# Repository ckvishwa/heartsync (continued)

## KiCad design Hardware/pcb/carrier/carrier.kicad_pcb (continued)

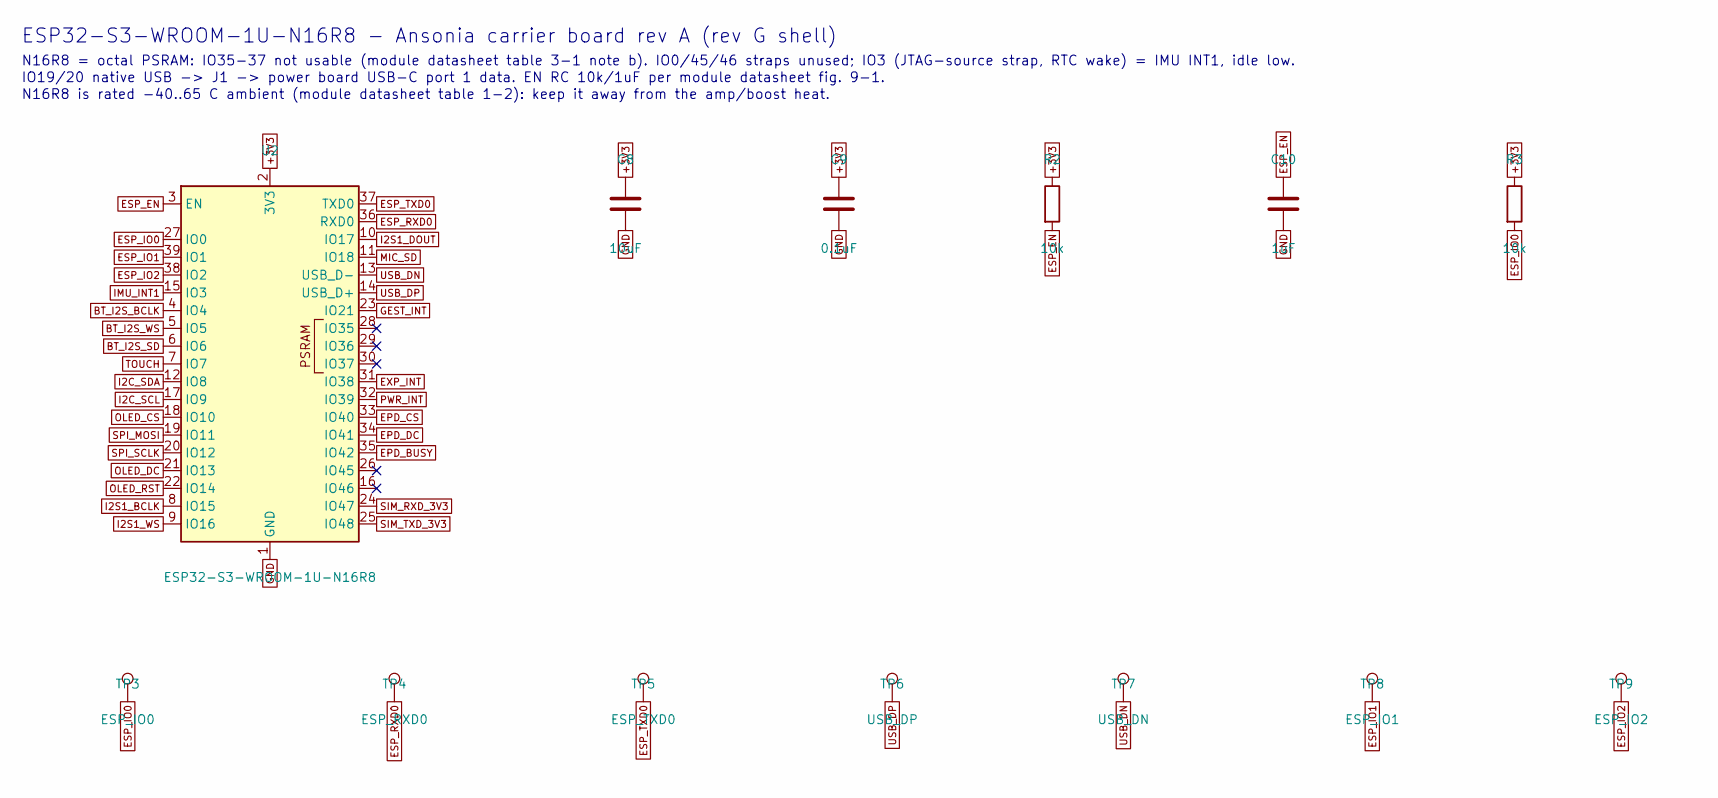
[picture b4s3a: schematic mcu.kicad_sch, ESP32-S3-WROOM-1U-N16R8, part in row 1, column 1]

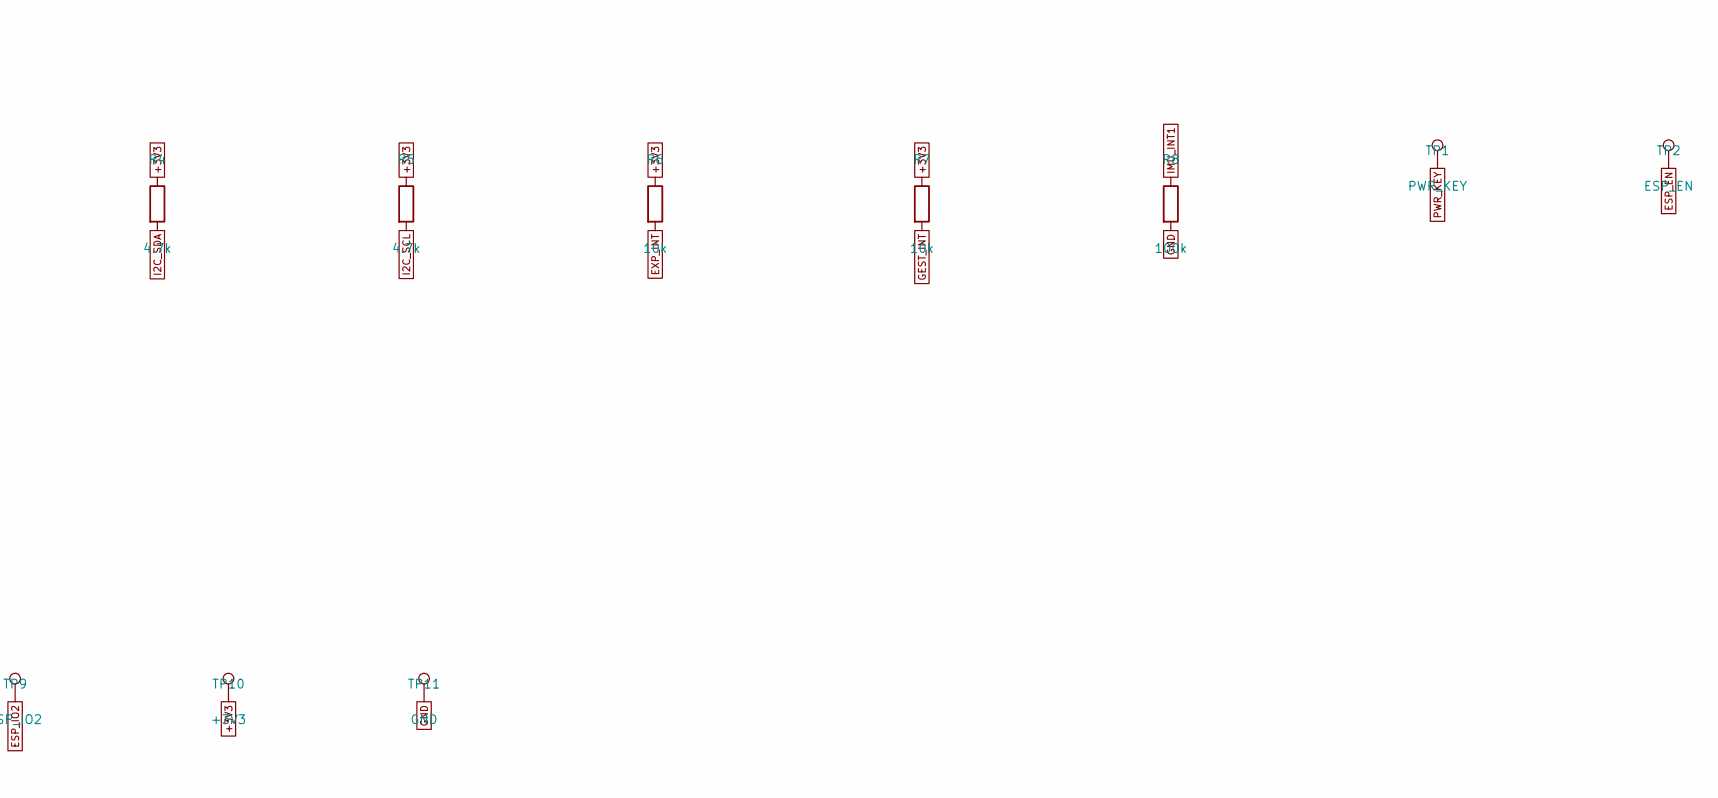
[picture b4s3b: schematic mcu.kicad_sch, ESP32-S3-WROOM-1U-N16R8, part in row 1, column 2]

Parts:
C8: 10uF; C_0603_1608Metric
C9: 0.1uF; C_0402_1005Metric
C10: 1uF; C_0402_1005Metric
R2, R3, R6, R7: 10k; R_0402_1005Metric
R4, R5: 4.7k; R_0402_1005Metric
R8: 100k; R_0402_1005Metric
TP1: PWR_KEY; TestPoint_Pad_D1.0mm
TP2: ESP_EN; TestPoint_Pad_D1.0mm
TP3: ESP_IO0; TestPoint_Pad_D1.0mm
TP4: ESP_RXD0; TestPoint_Pad_D1.0mm
TP5: ESP_TXD0; TestPoint_Pad_D1.0mm
TP6: USB_DP; TestPoint_Pad_D1.0mm
TP7: USB_DN; TestPoint_Pad_D1.0mm
TP8: ESP_IO1; TestPoint_Pad_D1.0mm
TP9: ESP_IO2; TestPoint_Pad_D1.0mm
TP10: +3V3; TestPoint_Pad_D1.0mm
TP11: GND; TestPoint_Pad_D1.0mm
U2: ESP32-S3-WROOM-1U-N16R8; ESP32-S3-WROOM-1U_NoVias; MPN ESP32-S3-WROOM-1U-N16R8; LCSC C3013946

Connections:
+3V3: C8.1, C9.1, R2.1, R3.1, R4.1, R5.1, R6.1, R7.1, TP10.1, U2.2 (3V3); also elsewhere on the board
BT_I2S_BCLK: U2.4 (IO4); also elsewhere on the board
BT_I2S_SD: U2.6 (IO6); also elsewhere on the board
BT_I2S_WS: U2.5 (IO5); also elsewhere on the board
EPD_BUSY: U2.35 (IO42); also elsewhere on the board
EPD_CS: U2.33 (IO40); also elsewhere on the board
EPD_DC: U2.34 (IO41); also elsewhere on the board
ESP_EN: C10.1, R2.2, TP2.1, U2.3 (EN)
ESP_IO0: R3.2, TP3.1, U2.27 (IO0)
ESP_IO1: TP8.1, U2.39 (IO1)
ESP_IO2: TP9.1, U2.38 (IO2)
ESP_RXD0: TP4.1, U2.36 (RXD0)
ESP_TXD0: TP5.1, U2.37 (TXD0)
EXP_INT: R6.2, U2.31 (IO38); also elsewhere on the board
GEST_INT: R7.2, U2.23 (IO21); also elsewhere on the board
GND: C8.2, C9.2, C10.2, R8.2, TP11.1, U2.1 (GND), U2.40 (GND), U2.41 (GND); also elsewhere on the board
I2C_SCL: R5.2, U2.17 (IO9); also elsewhere on the board
I2C_SDA: R4.2, U2.12 (IO8); also elsewhere on the board
I2S1_BCLK: U2.8 (IO15); also elsewhere on the board
I2S1_DOUT: U2.10 (IO17); also elsewhere on the board
I2S1_WS: U2.9 (IO16); also elsewhere on the board
IMU_INT1: R8.1, U2.15 (IO3); also elsewhere on the board
MIC_SD: U2.11 (IO18); also elsewhere on the board
OLED_CS: U2.18 (IO10); also elsewhere on the board
OLED_DC: U2.21 (IO13); also elsewhere on the board
OLED_RST: U2.22 (IO14); also elsewhere on the board
PWR_INT: U2.32 (IO39); also elsewhere on the board
PWR_KEY: TP1.1; also elsewhere on the board
SIM_RXD_3V3: U2.24 (IO47); also elsewhere on the board
SIM_TXD_3V3: U2.25 (IO48); also elsewhere on the board
SPI_MOSI: U2.19 (IO11); also elsewhere on the board
SPI_SCLK: U2.20 (IO12); also elsewhere on the board
TOUCH: U2.7 (IO7); also elsewhere on the board
USB_DN: TP7.1, U2.13 (USB_D-); also elsewhere on the board
USB_DP: TP6.1, U2.14 (USB_D+); also elsewhere on the board

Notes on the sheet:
ESP32-S3-WROOM-1U-N16R8 - Ansonia carrier board rev A (rev G shell)
N16R8 = octal PSRAM: IO35-37 not usable (module datasheet table 3-1 note b). IO0/45/46 straps unused; IO3 (JTAG-source strap, RTC wake) = IMU INT1, idle low.
IO19/20 native USB -> J1 -> power board USB-C port 1 data. EN RC 10k/1uF per module datasheet fig. 9-1.
N16R8 is rated -40..65 C ambient (module datasheet table 1-2): keep it away from the amp/boost heat.

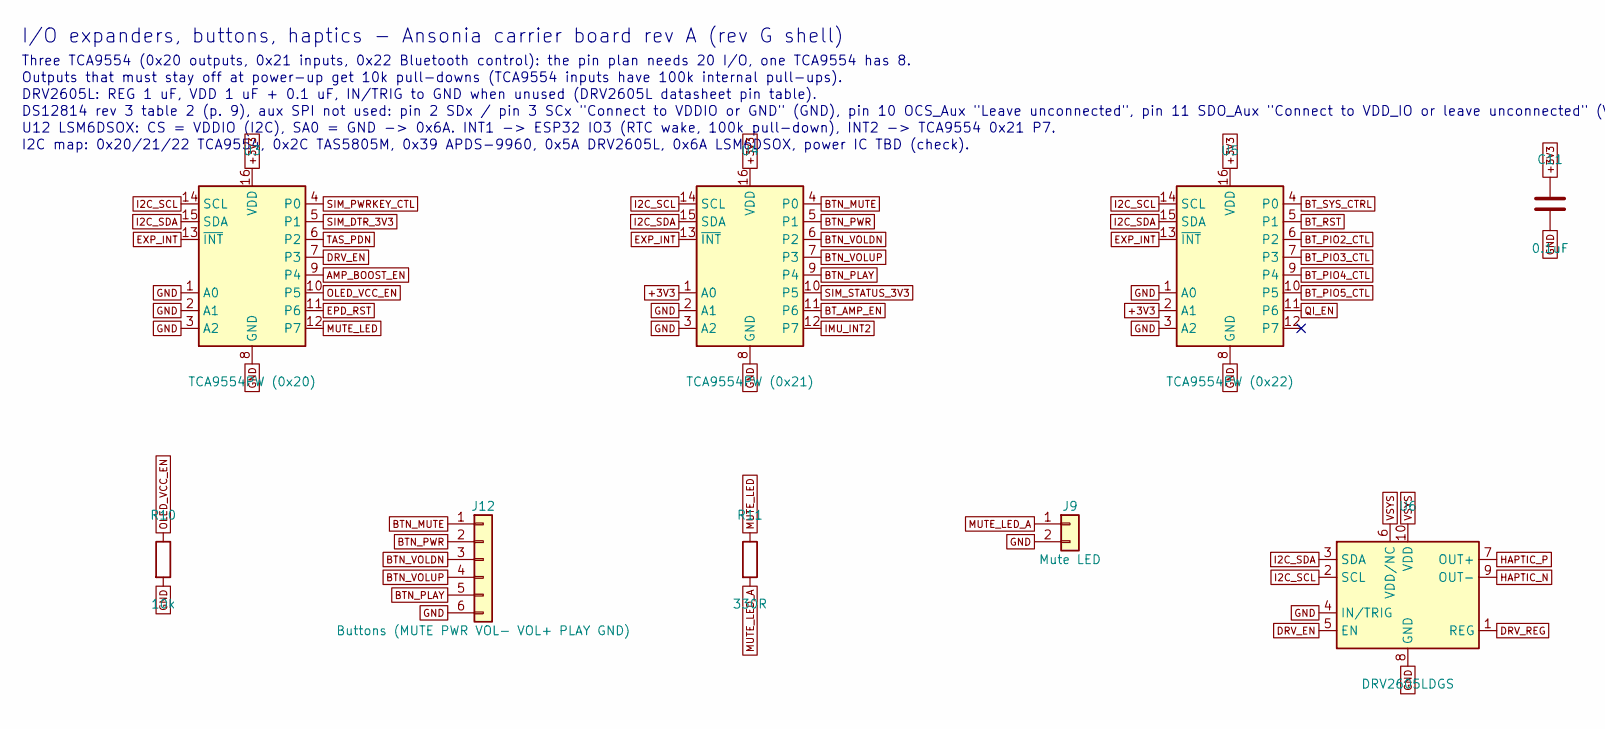
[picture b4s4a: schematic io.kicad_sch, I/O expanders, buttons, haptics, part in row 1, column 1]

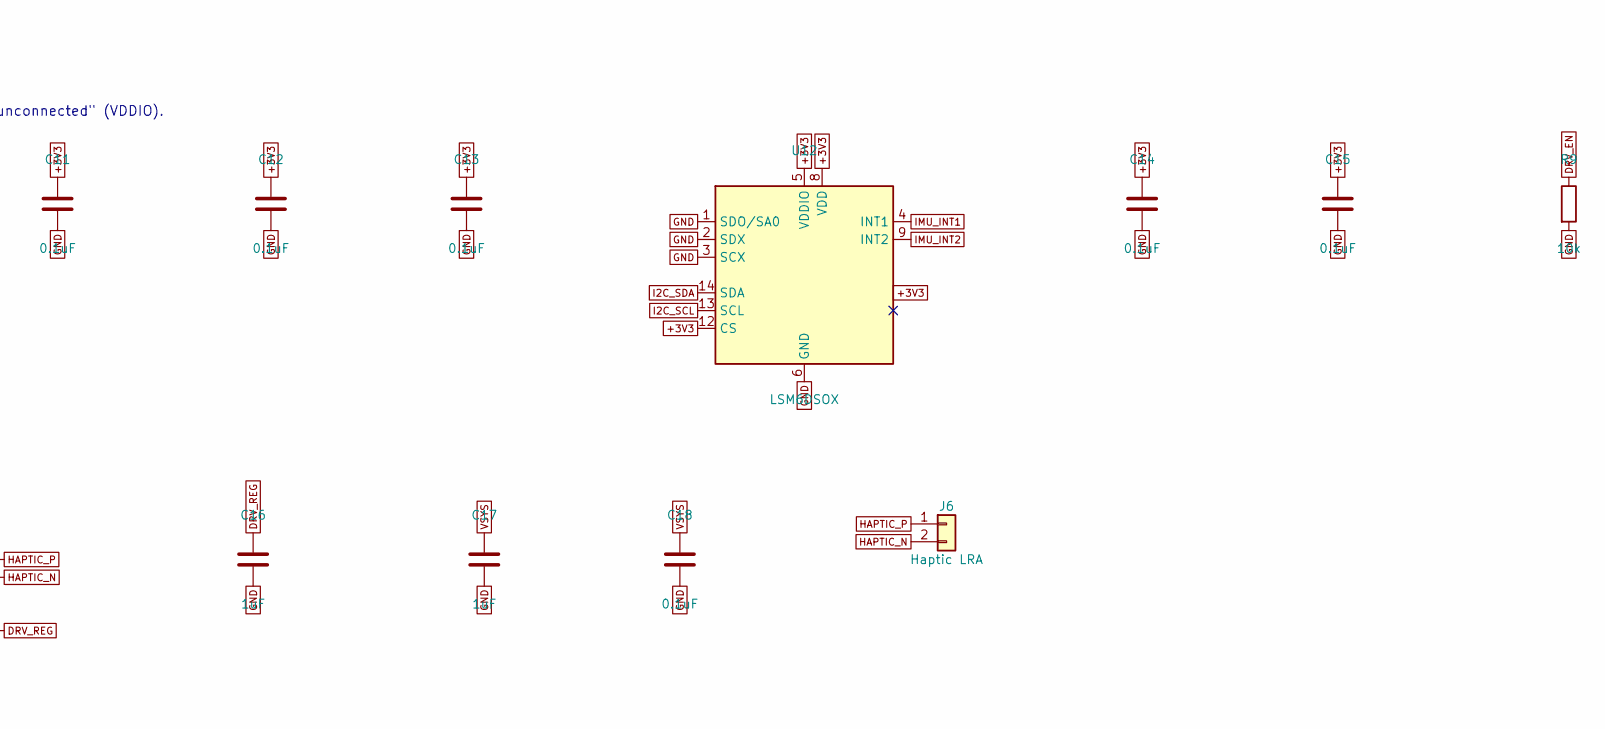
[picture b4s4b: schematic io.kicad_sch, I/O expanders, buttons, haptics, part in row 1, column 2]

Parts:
C11, C12, C13, C14, C15, C18: 0.1uF; C_0402_1005Metric
C16, C17: 1uF; C_0402_1005Metric
J6: Haptic LRA; JST_SH_SM02B-SRSS-TB_1x02-1MP_P1.00mm_Horizontal
J9: Mute LED; JST_SH_SM02B-SRSS-TB_1x02-1MP_P1.00mm_Horizontal
J12: Buttons (MUTE PWR VOL- VOL+ PLAY GND); JST_SH_SM06B-SRSS-TB_1x06-1MP_P1.00mm_Horizontal
R9, R10: 10k; R_0402_1005Metric
R11: 330R; R_0402_1005Metric
U3: TCA9554PW (0x20); TSSOP-16_4.4x5mm_P0.65mm; MPN TCA9554PWR; LCSC C86803
U4: TCA9554PW (0x21); TSSOP-16_4.4x5mm_P0.65mm; MPN TCA9554PWR; LCSC C86803
U5: TCA9554PW (0x22); TSSOP-16_4.4x5mm_P0.65mm; MPN TCA9554PWR; LCSC C86803
U6: DRV2605LDGS; TSSOP-10_3x3mm_P0.5mm; MPN DRV2605LDGSR; LCSC C527464
U12: LSM6DSOX; LGA-14_3x2.5mm_P0.5mm_LayoutBorder3x4y; MPN LSM6DSOXTR

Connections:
+3V3: C11.1, C12.1, C13.1, C14.1, C15.1, U3.16 (VDD), U4.1 (A0), U4.16 (VDD), U5.2 (A1), U5.16 (VDD), U12.5 (VDDIO), U12.8 (VDD), U12.11 (SDO_Aux), U12.12 (CS); also elsewhere on the board
AMP_BOOST_EN: U3.9 (P4); also elsewhere on the board
BTN_MUTE: J12.1, U4.4 (P0)
BTN_PLAY: J12.5, U4.9 (P4)
BTN_PWR: J12.2, U4.5 (P1)
BTN_VOLDN: J12.3, U4.6 (P2)
BTN_VOLUP: J12.4, U4.7 (P3)
BT_AMP_EN: U4.11 (P6); also elsewhere on the board
BT_PIO2_CTL: U5.6 (P2); also elsewhere on the board
BT_PIO3_CTL: U5.7 (P3); also elsewhere on the board
BT_PIO4_CTL: U5.9 (P4); also elsewhere on the board
BT_PIO5_CTL: U5.10 (P5); also elsewhere on the board
BT_RST: U5.5 (P1); also elsewhere on the board
BT_SYS_CTRL: U5.4 (P0); also elsewhere on the board
DRV_EN: R9.1, U3.7 (P3), U6.5 (EN)
DRV_REG: C16.1, U6.1 (REG)
EPD_RST: U3.11 (P6); also elsewhere on the board
EXP_INT: U3.13 (~INT), U4.13 (~INT), U5.13 (~INT); also elsewhere on the board
GND: C11.2, C12.2, C13.2, C14.2, C15.2, C16.2, C17.2, C18.2, J9.2, J12.6, R9.2, R10.2, U3.1 (A0), U3.2 (A1), U3.3 (A2), U3.8 (GND), U4.2 (A1), U4.3 (A2), U4.8 (GND), U5.1 (A0), U5.3 (A2), U5.8 (GND), U6.4 (IN/TRIG), U6.8 (GND), U12.1 (SDO/SA0), U12.2 (SDX), U12.3 (SCX), U12.6 (GND), U12.7 (GND); also elsewhere on the board
HAPTIC_N: J6.2, U6.9 (OUT-)
HAPTIC_P: J6.1, U6.7 (OUT+)
I2C_SCL: U3.14 (SCL), U4.14 (SCL), U5.14 (SCL), U6.2 (SCL), U12.13 (SCL); also elsewhere on the board
I2C_SDA: U3.15 (SDA), U4.15 (SDA), U5.15 (SDA), U6.3 (SDA), U12.14 (SDA); also elsewhere on the board
IMU_INT1: U12.4 (INT1); also elsewhere on the board
IMU_INT2: U4.12 (P7), U12.9 (INT2)
MUTE_LED: R11.1, U3.12 (P7)
MUTE_LED_A: J9.1, R11.2
OLED_VCC_EN: R10.1, U3.10 (P5); also elsewhere on the board
QI_EN: U5.11 (P6); also elsewhere on the board
SIM_DTR_3V3: U3.5 (P1); also elsewhere on the board
SIM_PWRKEY_CTL: U3.4 (P0); also elsewhere on the board
SIM_STATUS_3V3: U4.10 (P5); also elsewhere on the board
TAS_PDN: U3.6 (P2); also elsewhere on the board
VSYS: C17.1, C18.1, U6.6 (VDD/NC), U6.10 (VDD); also elsewhere on the board

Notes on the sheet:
I/O expanders, buttons, haptics - Ansonia carrier board rev A (rev G shell)
Three TCA9554 (0x20 outputs, 0x21 inputs, 0x22 Bluetooth control): the pin plan needs 20 I/O, one TCA9554 has 8.
Outputs that must stay off at power-up get 10k pull-downs (TCA9554 inputs have 100k internal pull-ups).
DRV2605L: REG 1 uF, VDD 1 uF + 0.1 uF, IN/TRIG to GND when unused (DRV2605L datasheet pin table).
DS12814 rev 3 table 2 (p. 9), aux SPI not used: pin 2 SDx / pin 3 SCx "Connect to VDDIO or GND" (GND), pin 10 OCS_Aux "Leave unconnected", pin 11 SDO_Aux "Connect to VDD_IO or leave unconnected" (VDDIO).
U12 LSM6DSOX: CS = VDDIO (I2C), SA0 = GND -> 0x6A. INT1 -> ESP32 IO3 (RTC wake, 100k pull-down), INT2 -> TCA9554 0x21 P7.
I2C map: 0x20/21/22 TCA9554, 0x2C TAS5805M, 0x39 APDS-9960, 0x5A DRV2605L, 0x6A LSM6DSOX, power IC TBD (check).

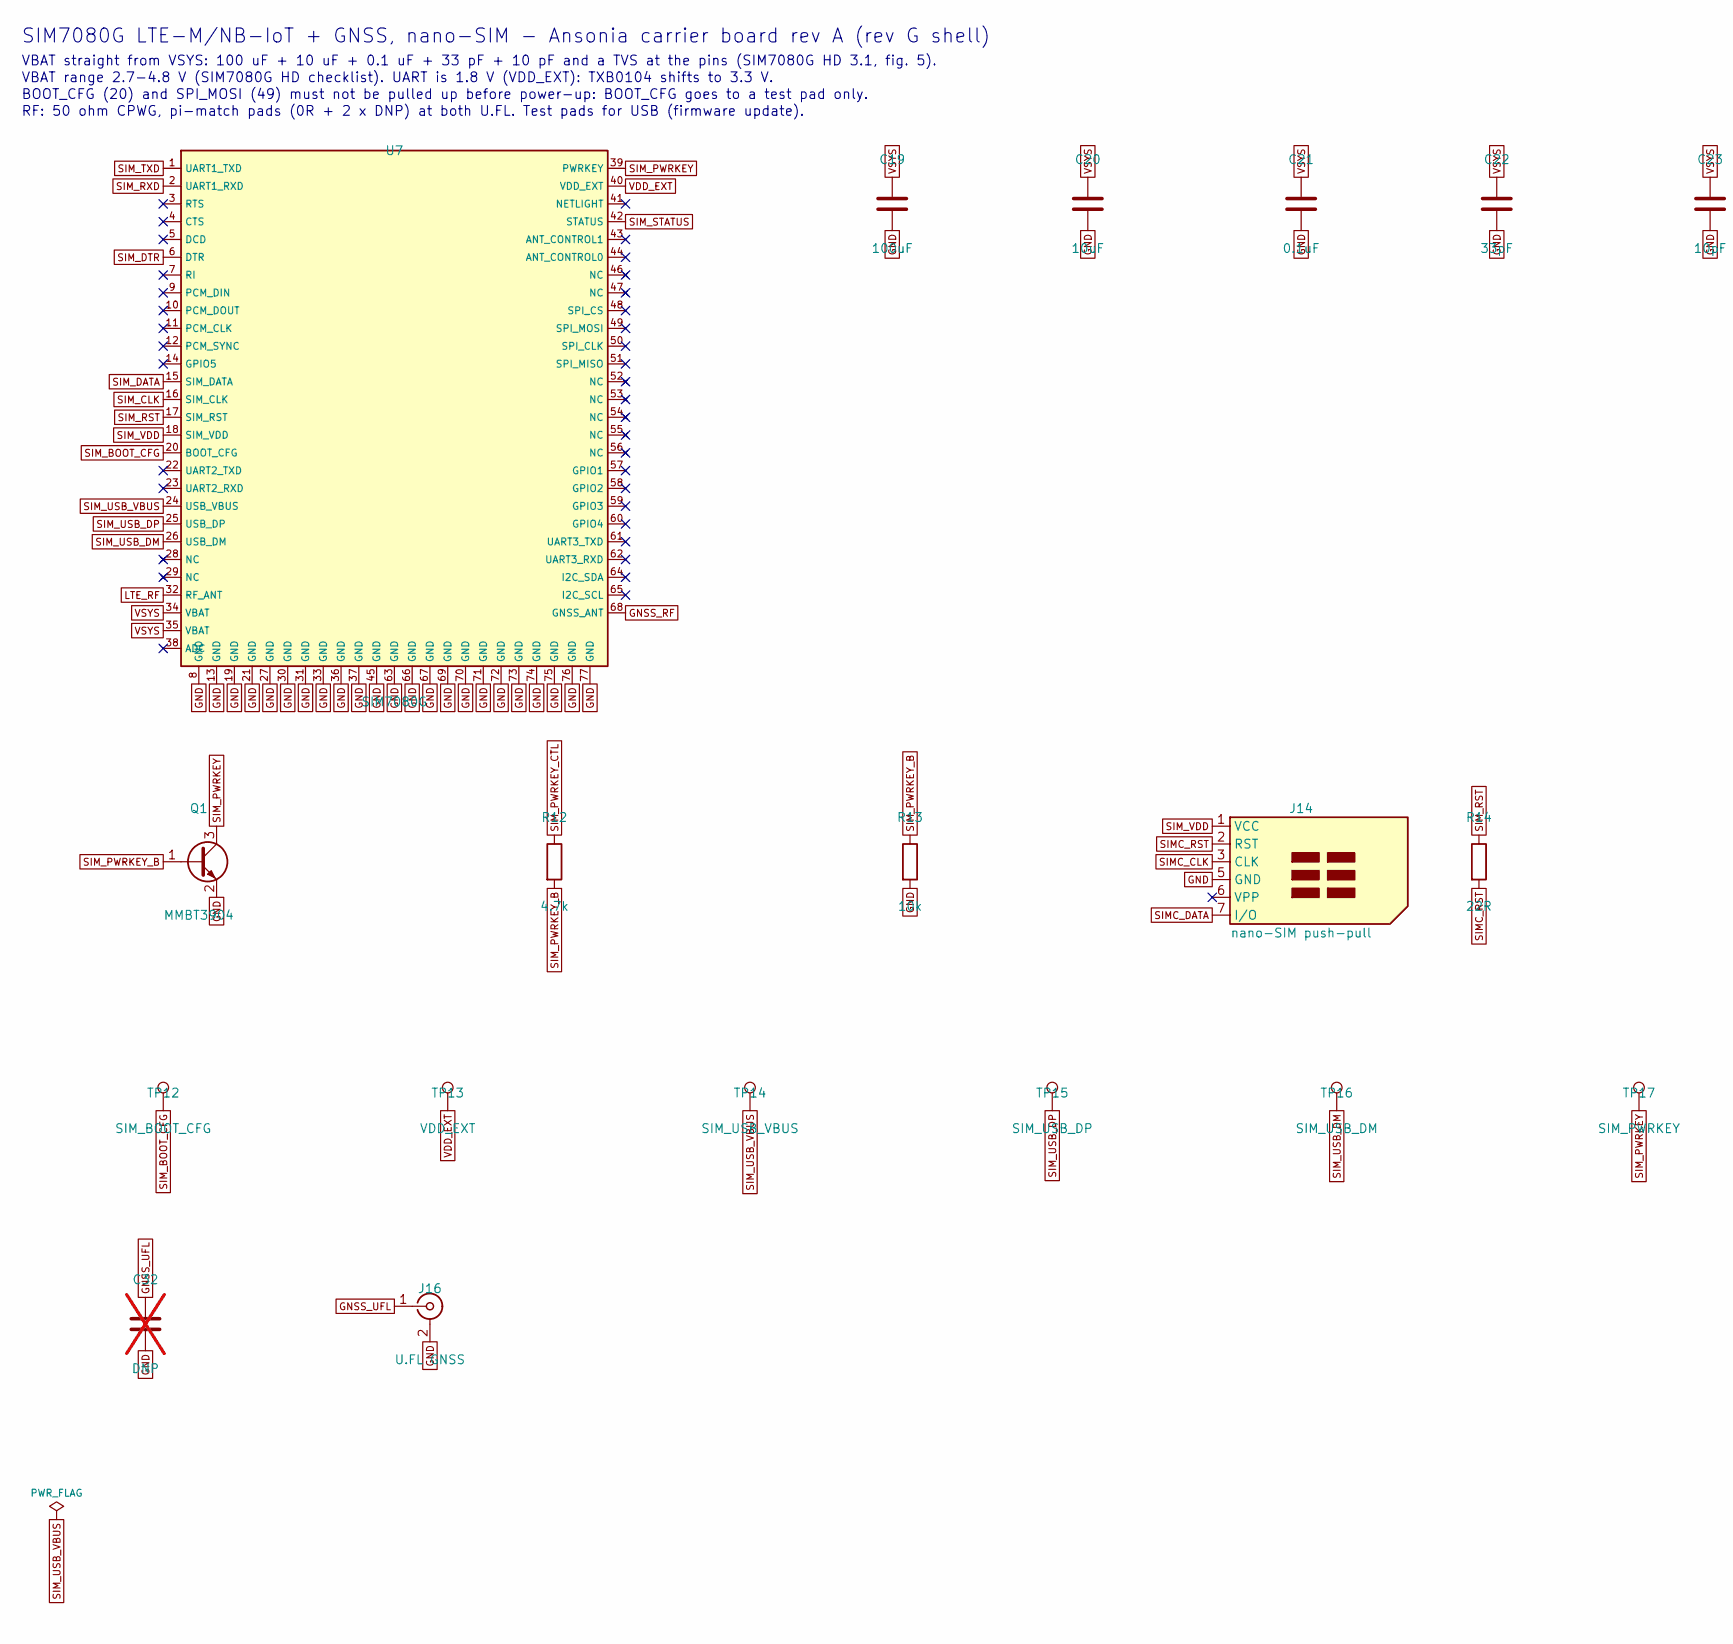
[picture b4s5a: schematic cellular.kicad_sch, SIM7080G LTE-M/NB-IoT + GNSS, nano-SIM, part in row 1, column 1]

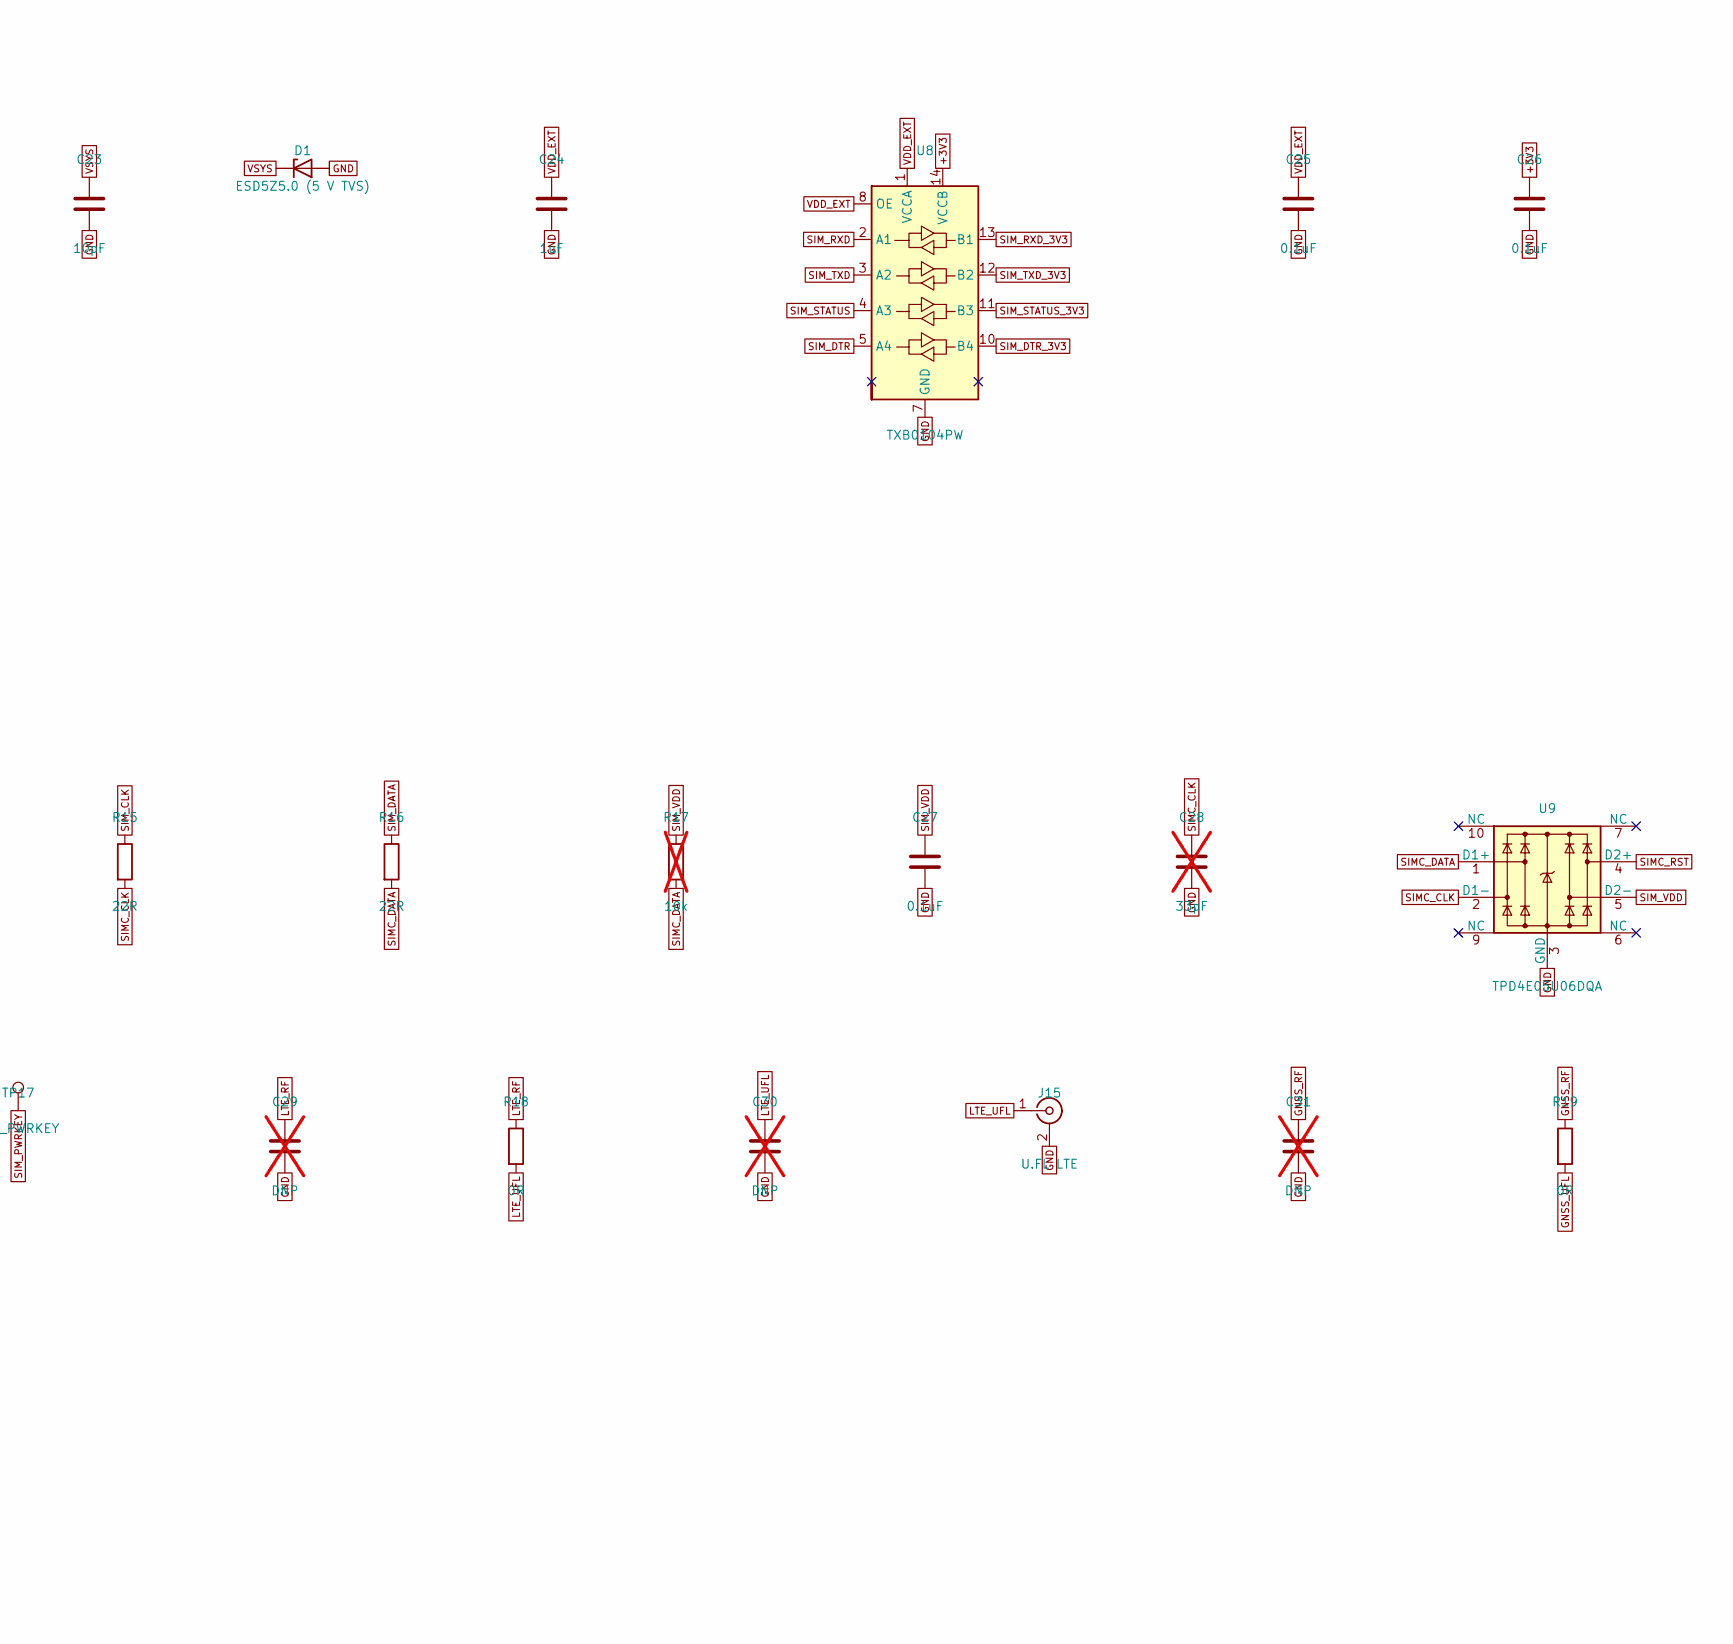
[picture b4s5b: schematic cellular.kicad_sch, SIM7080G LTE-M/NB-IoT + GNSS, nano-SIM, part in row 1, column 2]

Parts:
C19: 100uF; C_1210_3225Metric
C20: 10uF; C_0603_1608Metric
C21, C25, C26, C27: 0.1uF; C_0402_1005Metric
C22: 33pF; C_0402_1005Metric
C23: 10pF; C_0402_1005Metric
C24: 1uF; C_0402_1005Metric
C28: 33pF; C_0402_1005Metric; not fitted
C29, C30, C31, C32: DNP; C_0402_1005Metric; not fitted
D1: ESD5Z5.0 (5 V TVS); D_SOD-523
J14: nano-SIM push-pull; nanoSIM_GCT_SIM8060-6-0-14-00; MPN SIM8060-6-0-14-00-A
J15: U.FL LTE; U.FL_Hirose_U.FL-R-SMT-1_Vertical; MPN U.FL-R-SMT-1(10)
J16: U.FL GNSS; U.FL_Hirose_U.FL-R-SMT-1_Vertical; MPN U.FL-R-SMT-1(10)
Q1: MMBT3904; SOT-23
R12: 4.7k; R_0402_1005Metric
R13: 10k; R_0402_1005Metric
R14, R15, R16: 22R; R_0402_1005Metric
R17: 10k; R_0402_1005Metric; not fitted
R18, R19: 0R; R_0402_1005Metric
TP12: SIM_BOOT_CFG; TestPoint_Pad_D1.0mm
TP13: VDD_EXT; TestPoint_Pad_D1.0mm
TP14: SIM_USB_VBUS; TestPoint_Pad_D1.0mm
TP15: SIM_USB_DP; TestPoint_Pad_D1.0mm
TP16: SIM_USB_DM; TestPoint_Pad_D1.0mm
TP17: SIM_PWRKEY; TestPoint_Pad_D1.0mm
U7: SIM7080G; MPN SIM7080G; LCSC C2687012
U8: TXB0104PW; TSSOP-14_4.4x5mm_P0.65mm; MPN TXB0104PWR; LCSC C53406
U9: TPD4E05U06DQA; USON-10_2.5x1.0mm_P0.5mm; MPN TPD4E05U06DQAR

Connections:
+3V3: C26.1, U8.14 (VCCB); also elsewhere on the board
GND: C19.2, C20.2, C21.2, C22.2, C23.2, C24.2, C25.2, C26.2, C27.2, C28.2, C29.2, C30.2, C31.2, C32.2, D1.2 (A), J14.5 (GND), J15.2 (Ext), J16.2 (Ext), Q1.2 (E), R13.2, U7.8 (GND), U7.13 (GND), U7.19 (GND), U7.21 (GND), U7.27 (GND), U7.30 (GND), U7.31 (GND), U7.33 (GND), U7.36 (GND), U7.37 (GND), U7.45 (GND), U7.63 (GND), U7.66 (GND), U7.67 (GND), U7.69 (GND), U7.70 (GND), U7.71 (GND), U7.72 (GND), U7.73 (GND), U7.74 (GND), U7.75 (GND), U7.76 (GND), U7.77 (GND), U8.7 (GND), U9.3 (GND), U9.8 (GND); also elsewhere on the board
GNSS_RF: C31.1, R19.1, U7.68 (GNSS_ANT)
GNSS_UFL: C32.1, J16.1 (In), R19.2
LTE_RF: C29.1, R18.1, U7.32 (RF_ANT)
LTE_UFL: C30.1, J15.1 (In), R18.2
SIMC_CLK: C28.1, J14.3 (CLK), R15.2, U9.2 (D1-)
SIMC_DATA: J14.7 (I/O), R16.2, R17.2, U9.1 (D1+)
SIMC_RST: J14.2 (RST), R14.2, U9.4 (D2+)
SIM_BOOT_CFG: TP12.1, U7.20 (BOOT_CFG)
SIM_CLK: R15.1, U7.16 (SIM_CLK)
SIM_DATA: R16.1, U7.15 (SIM_DATA)
SIM_DTR: U7.6 (DTR), U8.5 (A4)
SIM_DTR_3V3: U8.10 (B4); also elsewhere on the board
SIM_PWRKEY: Q1.3 (C), TP17.1, U7.39 (PWRKEY)
SIM_PWRKEY_B: Q1.1 (B), R12.2, R13.1
SIM_PWRKEY_CTL: R12.1; also elsewhere on the board
SIM_RST: R14.1, U7.17 (SIM_RST)
SIM_RXD: U7.2 (UART1_RXD), U8.2 (A1)
SIM_RXD_3V3: U8.13 (B1); also elsewhere on the board
SIM_STATUS: U7.42 (STATUS), U8.4 (A3)
SIM_STATUS_3V3: U8.11 (B3); also elsewhere on the board
SIM_TXD: U7.1 (UART1_TXD), U8.3 (A2)
SIM_TXD_3V3: U8.12 (B2); also elsewhere on the board
SIM_USB_DM: TP16.1, U7.26 (USB_DM)
SIM_USB_DP: TP15.1, U7.25 (USB_DP)
SIM_USB_VBUS: TP14.1, U7.24 (USB_VBUS)
SIM_VDD: C27.1, J14.1 (VCC), R17.1, U7.18 (SIM_VDD), U9.5 (D2-)
VDD_EXT: C24.1, C25.1, TP13.1, U7.40 (VDD_EXT), U8.1 (VCCA), U8.8 (OE)
VSYS: C19.1, C20.1, C21.1, C22.1, C23.1, D1.1 (K), U7.34 (VBAT), U7.35 (VBAT); also elsewhere on the board

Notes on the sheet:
SIM7080G LTE-M/NB-IoT + GNSS, nano-SIM - Ansonia carrier board rev A (rev G shell)
VBAT straight from VSYS: 100 uF + 10 uF + 0.1 uF + 33 pF + 10 pF and a TVS at the pins (SIM7080G HD 3.1, fig. 5).
VBAT range 2.7-4.8 V (SIM7080G HD checklist). UART is 1.8 V (VDD_EXT): TXB0104 shifts to 3.3 V.
BOOT_CFG (20) and SPI_MOSI (49) must not be pulled up before power-up: BOOT_CFG goes to a test pad only.
RF: 50 ohm CPWG, pi-match pads (0R + 2 x DNP) at both U.FL. Test pads for USB (firmware update).

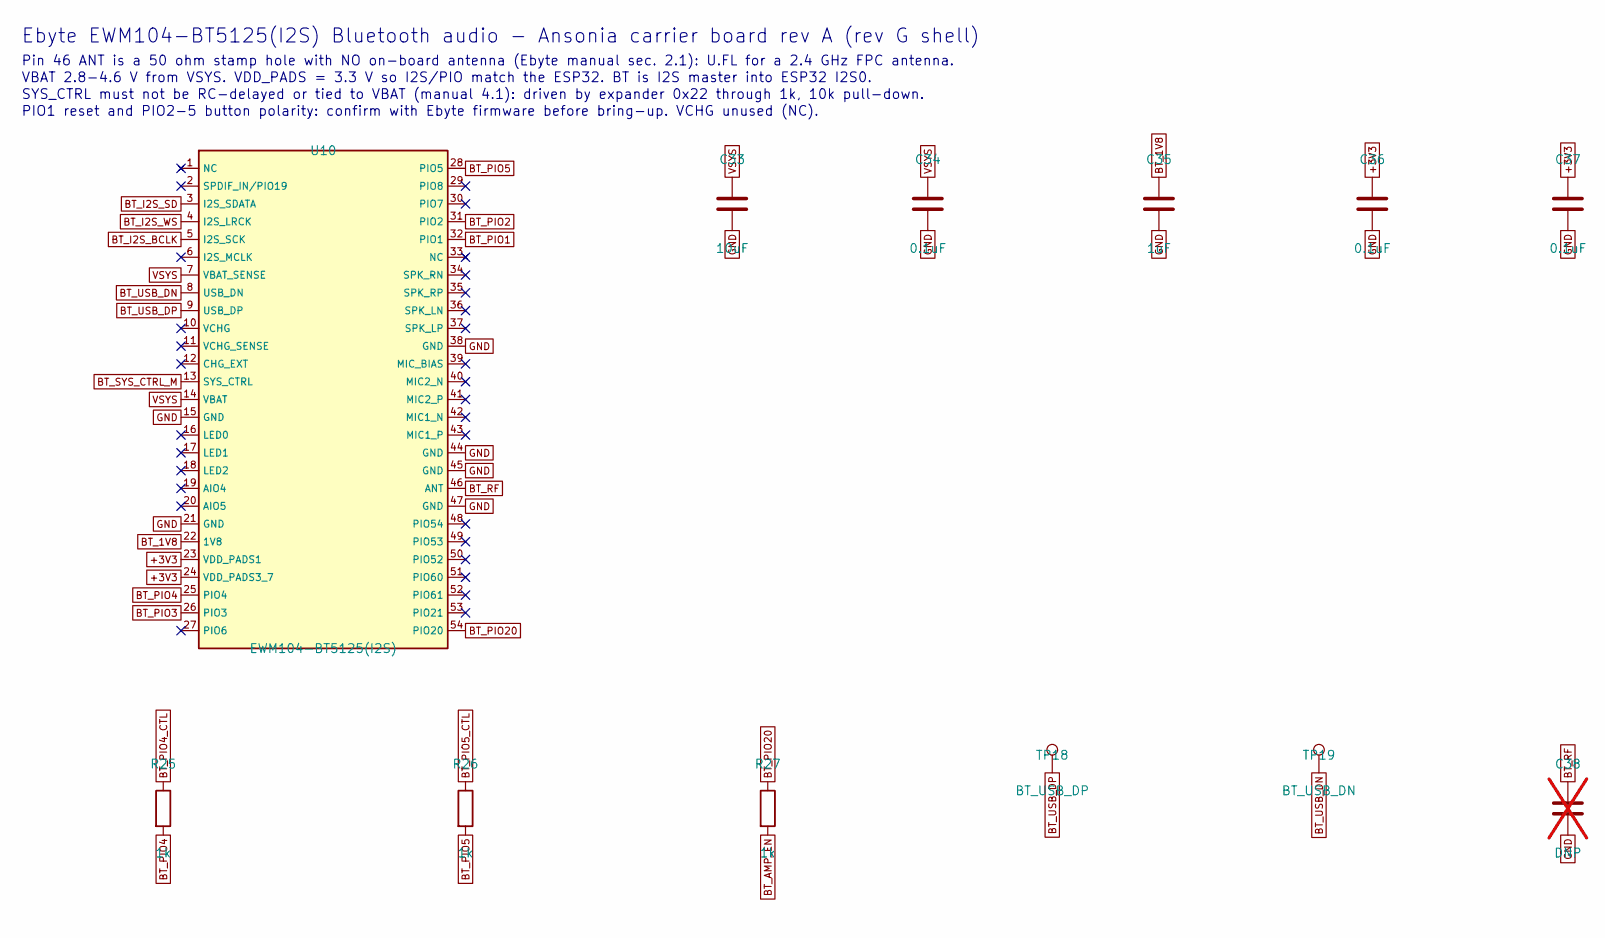
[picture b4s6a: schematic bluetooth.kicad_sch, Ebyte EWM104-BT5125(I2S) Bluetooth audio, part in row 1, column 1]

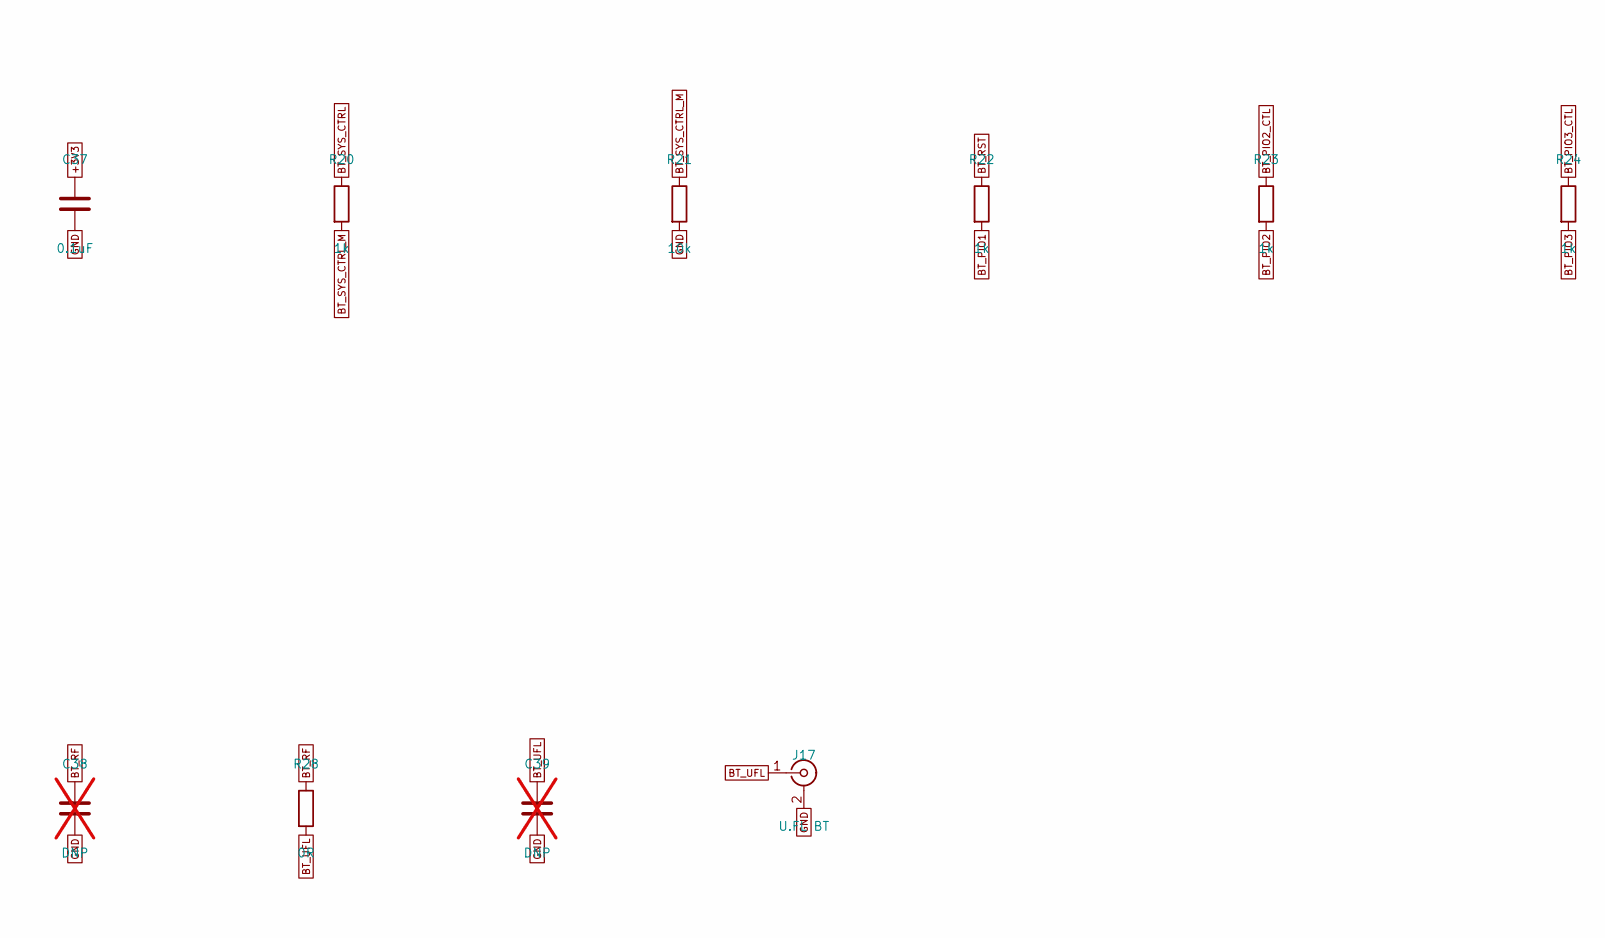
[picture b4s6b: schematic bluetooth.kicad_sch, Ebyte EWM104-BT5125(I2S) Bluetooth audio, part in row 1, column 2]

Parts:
C33: 10uF; C_0603_1608Metric
C34, C36, C37: 0.1uF; C_0402_1005Metric
C35: 1uF; C_0402_1005Metric
C38, C39: DNP; C_0402_1005Metric; not fitted
J17: U.FL BT; U.FL_Hirose_U.FL-R-SMT-1_Vertical; MPN U.FL-R-SMT-1(10)
R20, R22, R23, R24, R25, R26, R27: 1k; R_0402_1005Metric
R21: 10k; R_0402_1005Metric
R28: 0R; R_0402_1005Metric
TP18: BT_USB_DP; TestPoint_Pad_D1.0mm
TP19: BT_USB_DN; TestPoint_Pad_D1.0mm
U10: EWM104-BT5125(I2S); EWM104-BT5125; MPN EWM104-BT5125(I2S)

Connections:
+3V3: C36.1, C37.1, U10.23 (VDD_PADS1), U10.24 (VDD_PADS3_7); also elsewhere on the board
BT_1V8: C35.1, U10.22 (1V8)
BT_AMP_EN: R27.2; also elsewhere on the board
BT_I2S_BCLK: U10.5 (I2S_SCK); also elsewhere on the board
BT_I2S_SD: U10.3 (I2S_SDATA); also elsewhere on the board
BT_I2S_WS: U10.4 (I2S_LRCK); also elsewhere on the board
BT_PIO1: R22.2, U10.32 (PIO1)
BT_PIO2: R23.2, U10.31 (PIO2)
BT_PIO2_CTL: R23.1; also elsewhere on the board
BT_PIO3: R24.2, U10.26 (PIO3)
BT_PIO3_CTL: R24.1; also elsewhere on the board
BT_PIO4: R25.2, U10.25 (PIO4)
BT_PIO4_CTL: R25.1; also elsewhere on the board
BT_PIO5: R26.2, U10.28 (PIO5)
BT_PIO5_CTL: R26.1; also elsewhere on the board
BT_PIO20: R27.1, U10.54 (PIO20)
BT_RF: C38.1, R28.1, U10.46 (ANT)
BT_RST: R22.1; also elsewhere on the board
BT_SYS_CTRL: R20.1; also elsewhere on the board
BT_SYS_CTRL_M: R20.2, R21.1, U10.13 (SYS_CTRL)
BT_UFL: C39.1, J17.1 (In), R28.2
BT_USB_DN: TP19.1, U10.8 (USB_DN)
BT_USB_DP: TP18.1, U10.9 (USB_DP)
GND: C33.2, C34.2, C35.2, C36.2, C37.2, C38.2, C39.2, J17.2 (Ext), R21.2, U10.15 (GND), U10.21 (GND), U10.38 (GND), U10.44 (GND), U10.45 (GND), U10.47 (GND); also elsewhere on the board
VSYS: C33.1, C34.1, U10.7 (VBAT_SENSE), U10.14 (VBAT); also elsewhere on the board

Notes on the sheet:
Ebyte EWM104-BT5125(I2S) Bluetooth audio - Ansonia carrier board rev A (rev G shell)
Pin 46 ANT is a 50 ohm stamp hole with NO on-board antenna (Ebyte manual sec. 2.1): U.FL for a 2.4 GHz FPC antenna.
VBAT 2.8-4.6 V from VSYS. VDD_PADS = 3.3 V so I2S/PIO match the ESP32. BT is I2S master into ESP32 I2S0.
SYS_CTRL must not be RC-delayed or tied to VBAT (manual 4.1): driven by expander 0x22 through 1k, 10k pull-down.
PIO1 reset and PIO2-5 button polarity: confirm with Ebyte firmware before bring-up. VCHG unused (NC).
